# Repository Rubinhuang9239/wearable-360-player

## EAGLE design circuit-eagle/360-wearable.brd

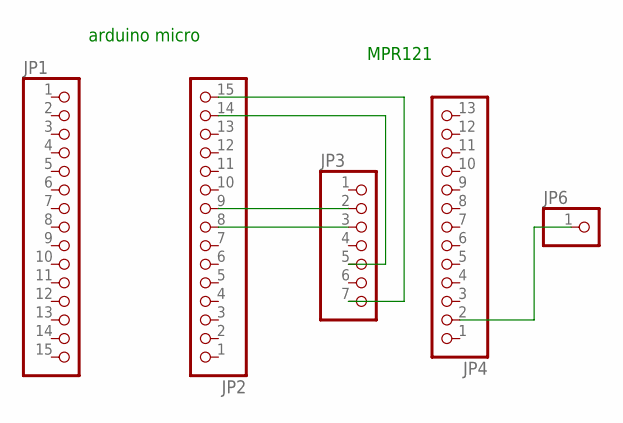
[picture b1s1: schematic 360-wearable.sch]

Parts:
JP1, JP2: PINHD-1X15; 1X15
JP3: PINHD-1X7; 1X07
JP4: PINHD-1X13; 1X13
JP6: PINHD-1X1; 1X01

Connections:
unnamed: JP4.2, JP6.1
unnamed: JP2.15, JP3.7
unnamed: JP2.14, JP3.5
unnamed: JP2.9, JP3.2
unnamed: JP2.8, JP3.3

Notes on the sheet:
arduino micro
MPR121

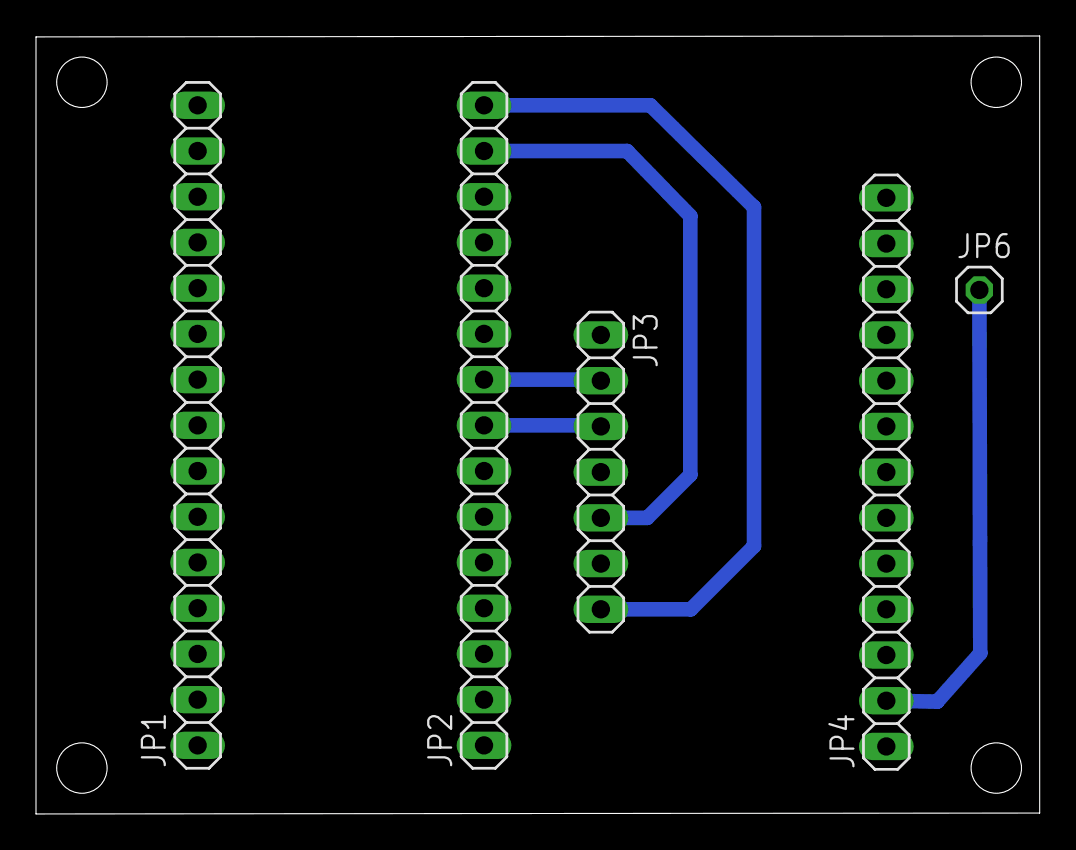
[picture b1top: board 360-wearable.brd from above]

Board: 2 copper layers, 55.8 x 43.2 mm, 5 parts (0 on the bottom side), 5 nets.

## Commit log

2017-09-27 First-commit
2017-09-30 Add circuit build
